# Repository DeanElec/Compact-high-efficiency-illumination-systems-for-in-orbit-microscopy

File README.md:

# Compact-high-efficiency-illumination-systems-for-in-orbit-microscopy
Presents all data associated with the development of my thesis for a 3rd year final year project at the University of Nottingham
***
## Project Overview
The aim of the project was to develop a solution to image specimens such as C. elegans and similar sized organisms in bright field and darkfield modalities, that would fit in a 1U Cube Sat (10cm^3) for less than £200.

***
## Project Evaluation
The project overall was a success as the system was able to take both bright field and dark field images with high enough resolution and resolving power to accurate image Diatoms, C.elegans and Buccal Epithelial Cells, however the code was not developed to run autonomously but the code developed for the Raspberry Pi as part of the GUI control could be quickly and easily modified to make a autonomous system due directly relevent code wrote in a generic way such that it can be reused.

Due to cost restraint a set of cheap lenses were used, but the datasheet that came with these lenses had all incorrect parameters such as FOV or MOD. For this reason significant time was spent characterising the lenses so the data could be relied upon.

For full evaluation of the design and the data my thesis can be found in the thesis directory.

### Images Taken on the Microscope
***
#### Diatoms Bright and Dark Field

#### Buccal Epithelial Cells Bright and Dark Field

***

### CAD Images of the Microscope System
***

***

## Control Interface
For ease of testing / taking images with the microscope a GUI was developed in C++ using QT to control all aspects of the microscope remotely when connected on the same network. This allowed for control of:
- Automatic transfer of the images taken on the Raspberry Pi to the host PC
- Save directory locations for both the Raspberry Pi side and the host PC side for saving the recieved images from the Raspberry Pi
- Brightness and PWM frequency controll of all 3 colour rings plus the central cyan LED used for rhinefield illumination
- Multiple basic (binary) image processing options such as the type of demosaic algorithm, and others
- Advanced image processing options such as custom brightness, white balance and gamma options
- Finally a button to allow the user to take an image once parameters have been set by the user

## Future Work / Improvements
If this project was to be taken forward, the current PCB's would work but really require a PCB assembly house to manufacture and populate the board as it is too densely packed with too small component to do by hand and was a main struggle in the project.

That said an improved design for the illumination board has already been created and tested based on addressable SK6805 LEDs and will be uploaded to this github repo in the future once the driver board for it has been finalised and tested.
The new design will be able to be controlled via a plug-in for the open source microscopy software micro-manager, it will provide a GUI that will allow the user to control the illumination system from the host PC running micro-manager, as micro-manager
was wrote in java it is inherently cross platform and thus the plug-in should work for any OS.

Also as potential future upgrades would be to add a form of auto focus as although the microscope worked and gathered detailed images it was hard to get the specimens in focus.
***

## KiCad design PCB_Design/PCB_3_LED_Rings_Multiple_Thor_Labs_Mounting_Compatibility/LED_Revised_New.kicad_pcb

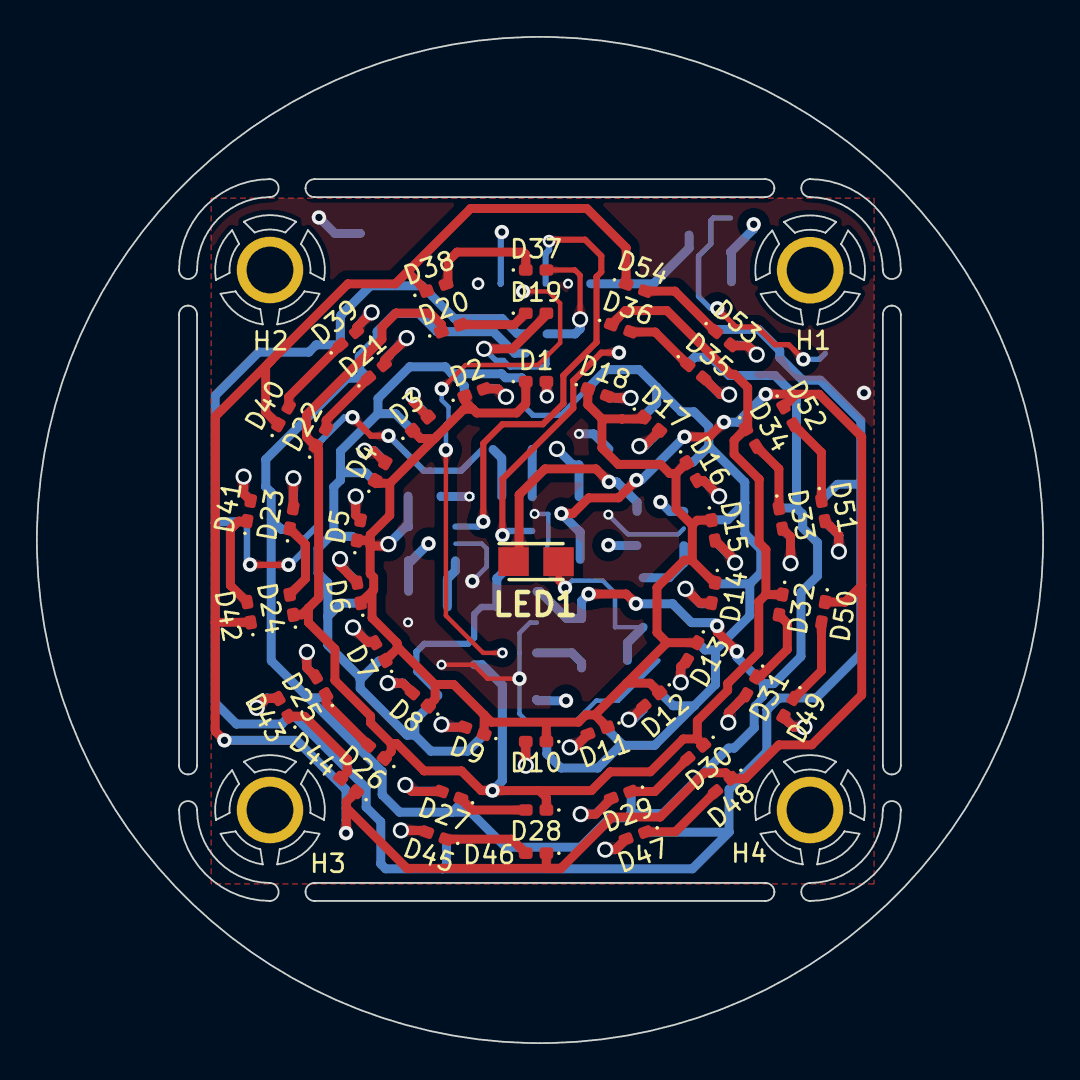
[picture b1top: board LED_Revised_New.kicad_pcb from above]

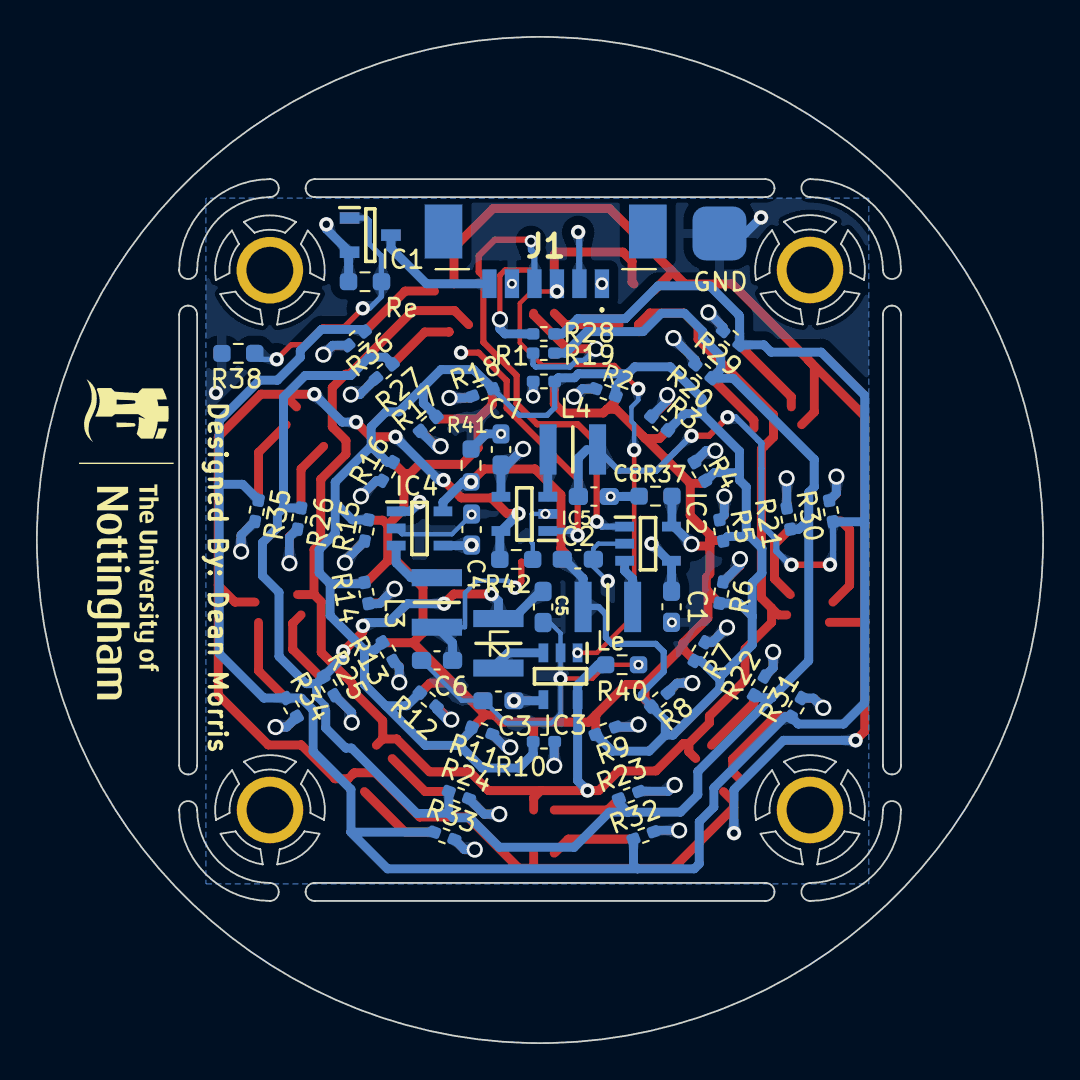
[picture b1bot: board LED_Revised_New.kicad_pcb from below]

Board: 4 copper layers, 55.9 x 55.9 mm, 120 parts (61 on the bottom side), 74 nets.

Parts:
C1, C2, C3, C4, C5, C6, C7, C8: 10uF; C_0603_1608Metric_Pad1.08x0.95mm_HandSolder
D1, D2, D3, D4, D5, D6, D7, D8, D9, D10, D11, D12, D13, D14, D15, D16, D17, D18, D19, D20, D21, D22, D23, D24, D25, D26, D27, D28, D29, D30, D31, D32, D33, D34, D35, D36, D37, D38, D39, D40, D41, D42, D43, D44, D45, D46, D47, D48, D49, D50, D51, D52, D53, D54: LED_0402_1005Metric_Pad0.77x0.64mm_HandSolder
H1, H2, H3, H4: MountingHole_Pad; M2.5_Mountinh_Hole
H6: SMD_Ground_Pad; 3mm_Ground_Pad
IC1: FDN360P; SOT95P251X112-3N
IC2, IC3, IC4, IC5: PAM2804AAB010; SOT95P280X100-5N
J1: Conn_01x06_Socket; 532610671
L2, L3, L4: 4.7uH; DFE322520FD1R0MP2
LED1: AA3021VRCBS_A; LEDM3020X150N
Le: 4.7uH; DFE322520FD1R0MP2
R1, R2, R3, R4, R5, R6, R7, R8, R9, R10, R11, R12, R13, R14, R15, R16, R17, R18, R19, R20, R21, R22, R23, R24, R25, R26, R27, R28, R29, R30, R31, R32, R33, R34, R35, R36: 100; R_0402_1005Metric_Pad0.72x0.64mm_HandSolder
R37, R40, R42: R; R_0603_1608Metric_Pad0.98x0.95mm_HandSolder
R38: 10k; R_0603_1608Metric_Pad0.98x0.95mm_HandSolder
R41: 3.6; R_0603_1608Metric_Pad0.98x0.95mm_HandSolder
Re: 10k; R_0603_1608Metric_Pad0.98x0.95mm_HandSolder

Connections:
/SW: IC4.3 (SW), L3.2
Blue_LED_End: D1.1 (K), D2.1 (K), D3.1 (K), D4.1 (K), D5.1 (K), D6.1 (K), D7.1 (K), D8.1 (K), D9.1 (K), D10.1 (K), D11.1 (K), D12.1 (K), D13.1 (K), D14.1 (K), D15.1 (K), D16.1 (K), D17.1 (K), D18.1 (K), IC2.5 (FB), R37.1
Blue_LED_Start: C2.1, Le.1, R1.1, R2.1, R3.1, R4.1, R5.1, R6.1, R7.1, R8.1, R9.1, R10.1, R11.1, R12.1, R13.1, R14.1, R15.1, R16.1, R17.1, R18.1
GND: C1.2, C2.2, C3.2, C4.2, C5.2, C6.2, C7.2, C8.2, H6.1, IC2.2 (GND), IC3.2 (GND), IC4.2 (GND), IC5.2 (GND), J1.5, R37.2, R38.1, R40.2, R41.2, R42.2
Green_LED_End: D20.1 (K), D22.1 (K), D24.1 (K), D26.1 (K), D28.1 (K), D30.1 (K), D32.1 (K), D34.1 (K), D36.1 (K), IC3.5 (FB), R40.1
Green_LED_Start: C5.1, L2.1, R19.1, R20.1, R21.1, R22.1, R23.1, R24.1, R25.1, R26.1, R27.1
unnamed: D1.2 (A), R1.2
unnamed: D2.2 (A), R2.2
unnamed: D3.2 (A), R3.2
unnamed: D4.2 (A), R4.2
unnamed: D5.2 (A), R5.2
unnamed: D6.2 (A), R6.2
unnamed: D7.2 (A), R7.2
unnamed: D8.2 (A), R8.2
unnamed: D9.2 (A), R9.2
unnamed: D10.2 (A), R10.2
unnamed: D11.2 (A), R11.2
unnamed: D12.2 (A), R12.2
unnamed: D13.2 (A), R13.2
unnamed: D14.2 (A), R14.2
unnamed: D15.2 (A), R15.2
unnamed: D16.2 (A), R16.2
unnamed: D17.2 (A), R17.2
unnamed: D18.2 (A), R18.2
unnamed: D19.2 (A), R19.2
unnamed: D19.1 (K), D20.2 (A)
unnamed: D21.2 (A), R20.2
unnamed: D21.1 (K), D22.2 (A)
unnamed: D23.2 (A), R21.2
unnamed: D23.1 (K), D24.2 (A)
unnamed: D25.2 (A), R22.2
unnamed: D25.1 (K), D26.2 (A)
unnamed: D27.2 (A), R23.2
unnamed: D27.1 (K), D28.2 (A)
unnamed: D29.2 (A), R24.2
unnamed: D29.1 (K), D30.2 (A)
unnamed: D31.2 (A), R25.2
unnamed: D31.1 (K), D32.2 (A)
unnamed: D33.2 (A), R26.2
unnamed: D33.1 (K), D34.2 (A)
unnamed: D35.2 (A), R27.2
unnamed: D35.1 (K), D36.2 (A)
unnamed: D37.2 (A), R28.2
unnamed: D37.1 (K), D38.2 (A)
unnamed: D39.2 (A), R29.2
unnamed: D39.1 (K), D40.2 (A)
unnamed: D41.2 (A), R30.2
unnamed: D41.1 (K), D42.2 (A)
unnamed: D43.2 (A), R31.2
unnamed: D43.1 (K), D44.2 (A)
unnamed: D45.2 (A), R32.2
unnamed: D45.1 (K), D46.2 (A)
unnamed: D47.2 (A), R33.2
unnamed: D47.1 (K), D48.2 (A)
unnamed: D49.2 (A), R34.2
unnamed: D49.1 (K), D50.2 (A)
unnamed: D51.2 (A), R35.2
unnamed: D51.1 (K), D52.2 (A)
unnamed: D53.2 (A), R36.2
unnamed: D53.1 (K), D54.2 (A)
unnamed: IC1.1 (G), R38.2, Re.1
unnamed: IC2.3 (SW), Le.2
unnamed: IC3.3 (SW), L2.2
unnamed: IC4.5 (FB), LED1.1 (K), R41.1
unnamed: IC5.3 (SW), L4.2
unnamed: C6.1, L3.1, LED1.2 (A)
PWM_Cyan_LED: IC4.1 (EN), J1.1
PWM_Inner_LED_RIng: IC2.1 (EN), J1.4
PWM_Middle_LED_RIng: IC3.1 (EN), J1.3
PWM_Outer_LED_Ring: IC5.1 (EN), J1.2
Red_LED_End: D38.1 (K), D40.1 (K), D42.1 (K), D44.1 (K), D46.1 (K), D48.1 (K), D50.1 (K), D52.1 (K), D54.1 (K), IC5.5 (FB), R42.1
Red_LED_Start: C8.1, L4.1, R28.1, R29.1, R30.1, R31.1, R32.1, R33.1, R34.1, R35.1, R36.1
Vin: IC1.3 (D), J1.6
Vin_Protected: C1.1, C3.1, C4.1, C7.1, IC1.2 (S), IC2.4 (VIN), IC3.4 (VIN), IC4.4 (VIN), IC5.4 (VIN), Re.2

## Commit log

2024-05-28 Create folder for CAD designs
2024-05-28 Version one Microscope Stand
2024-05-28 LED based illumination PCB for multi-modal imaging
    3 LED rings 18 LEDs per ring, one ring per imaging modality, allows for brightfield, darkfield and phase contrast. Also provides different mounting options such as Thor Labs 30 and 60mm cage plates, 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
    Note when tested wasnt fully functional, thought to be due to fact it was hand soldered with 0402 components with solder paste with no stencil. Its believed if professionally manufactured and populat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
2024-05-29 Folder for all code developed for the control of the microscope
2024-05-29 Code developed that runs on the Raspberry Pi 4
2024-05-29 All relevant file/code that runs on the raspberry pi 4
    Contains all code for the microscope control on the pi 4 side, including additional files such as memory tests and files for image processing including the cython code, setup.py file and the .SO file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
2024-05-29 Create QT Linux GUI
2024-05-29 All files for the QT Linux GUI
    QT GUI is a widget application, with all needed custom classed and additional files
